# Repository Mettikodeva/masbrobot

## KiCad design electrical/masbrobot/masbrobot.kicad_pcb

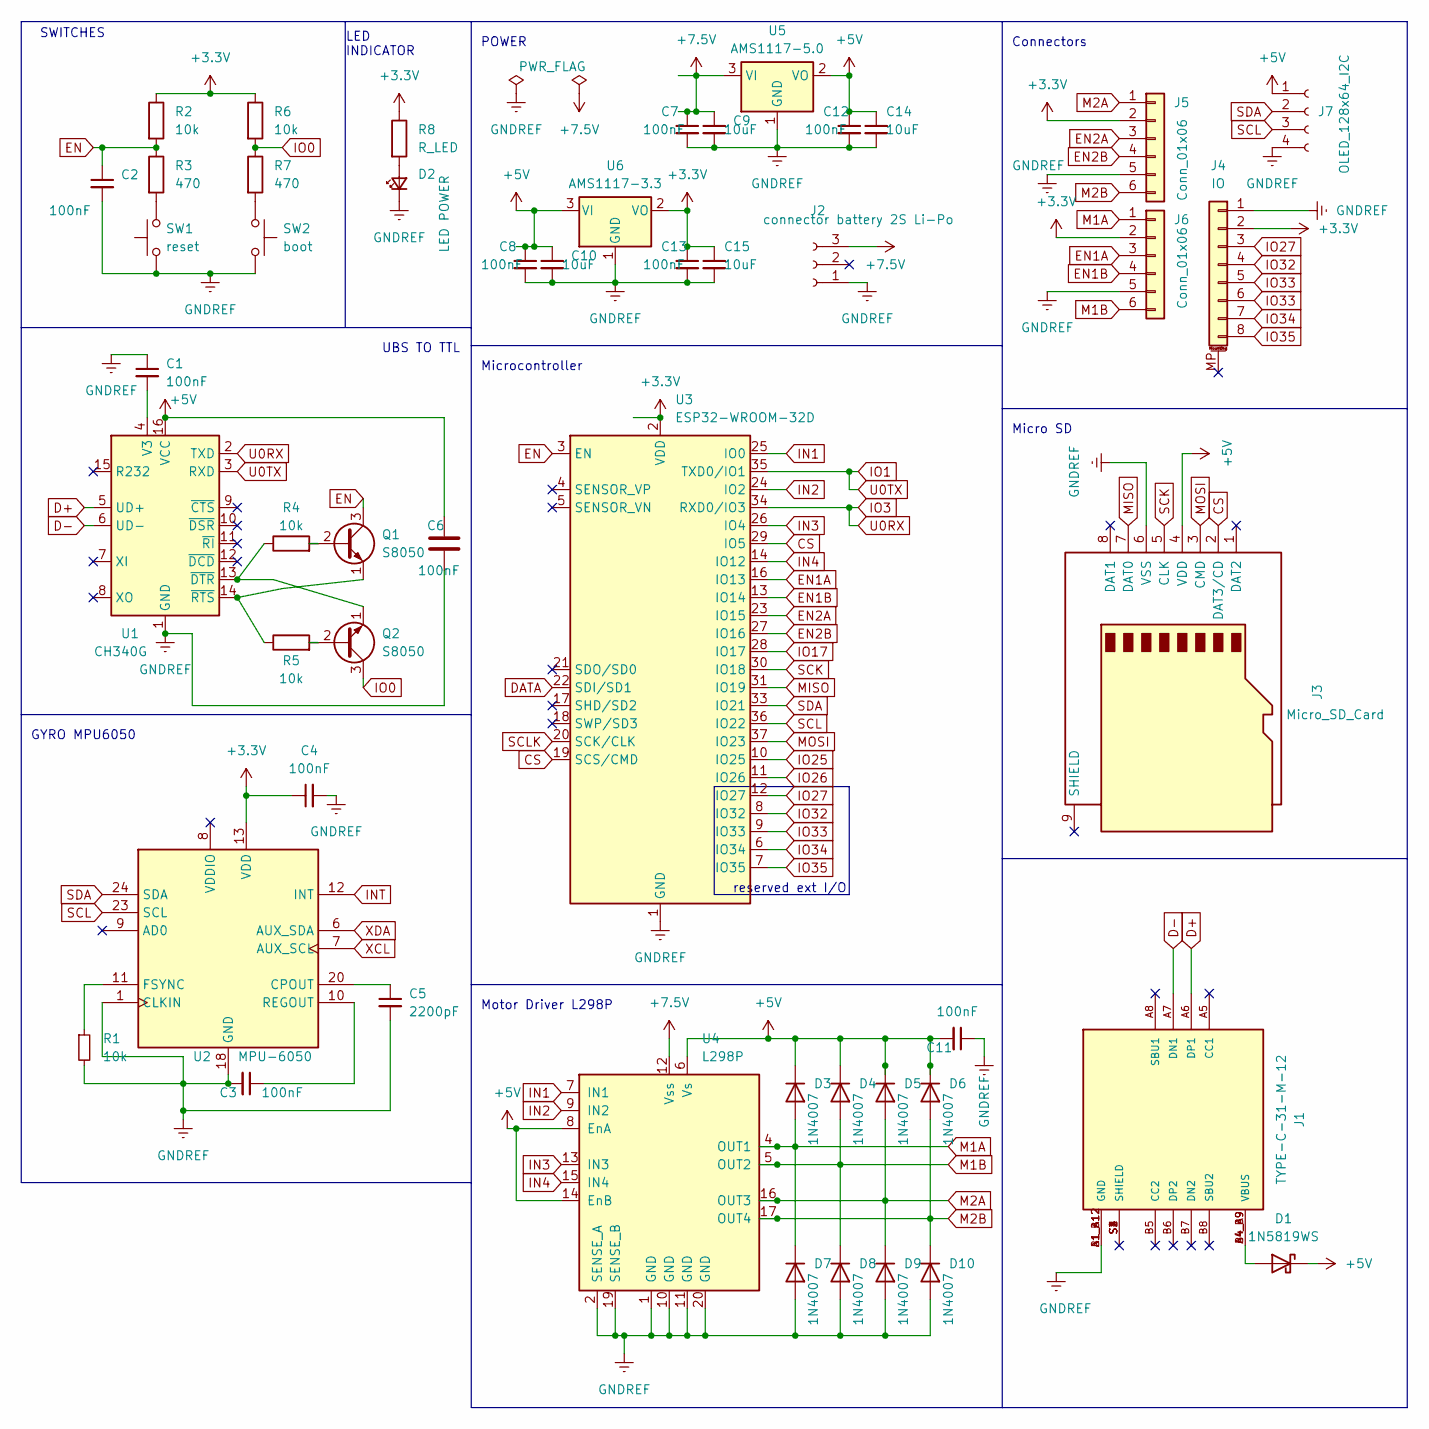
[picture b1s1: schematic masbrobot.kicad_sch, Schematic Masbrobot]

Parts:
C1, C2, C3, C4, C6, C7, C8, C11, C12, C13: 100nF; C_0805_2012Metric
C5: 2200pF; C_0805_2012Metric
C9, C10, C14, C15: 10uF; C_0201_0603Metric
D1: 1N5819WS; D_SOD-323
D2: LED POWER; LED_1206_3216Metric
D3, D4, D5, D6, D7, D8, D9, D10: 1N4007; D_0201_0603Metric
J1: TYPE-C-31-M-12; HRO_TYPE-C-31-M-12; PARTREV 2020.12.08
J2: connector battery 2S Li-Po; JST_XH_B3B-XH-A_1x03_P2.50mm_Vertical
J3: Micro_SD_Card; microSD_HC_Hirose_DM3BT-DSF-PEJS
J4: IO; PinHeader_1x08_P1.27mm_Horizontal
J5, J6: Conn_01x06; JST_GH_BM06B-GHS-TBT_1x06-1MP_P1.25mm_Vertical
J7: OLED_128x64_I2C; JST_GH_BM04B-GHS-TBT_1x04-1MP_P1.25mm_Vertical
Q1, Q2: S8050; TO-92_Inline
R1, R4, R5: 10k; R_0805_2012Metric
R2, R6: 10k; R_1206_3216Metric
R3, R7: 470; R_1206_3216Metric
R8: R_LED; R_0402_1005Metric
SW1: reset; SW_Tactile_SPST_NO_Straight_CK_PTS636Sx25SMTRLFS
SW2: boot; SW_Tactile_SPST_NO_Straight_CK_PTS636Sx25SMTRLFS
U1: CH340G; SOIC-16_3.9x9.9mm_P1.27mm
U2: MPU-6050; InvenSense_QFN-24_4x4mm_P0.5mm
U3: ESP32-WROOM-32D; ESP32-WROOM-32
U4: L298P; SOIC127P1420X360-20N
U5: AMS1117-5.0; SOT-223-3_TabPin2
U6: AMS1117-3.3; SOT-223-3_TabPin2

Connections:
+3.3V: C4.1, C13.1, C15.1, J4.2, J5.2, J6.2, R2.1, R6.1, R8.1, U2.13 (VDD), U3.2 (VDD), U6.2 (VO)
+5V: C6.1, C8.1, C10.1, C11.2, C12.1, C14.1, D1.1 (K), D3.1 (K), D4.1 (K), D5.1 (K), D6.1 (K), J3.4 (VDD), J7.1, U1.16 (VCC), U4.6 (Vs), U4.8 (EnA), U4.14 (EnB), U5.2 (VO), U6.3 (VI)
+7.5V: C7.1, C9.1, J2.3, U4.12 (Vss), U5.3 (VI)
CS: J3.2 (DAT3/CD), U3.19 (SCS/CMD), U3.29 (IO5)
D+: J1.A6 (DP1), U1.5 (UD+)
D-: J1.A7 (DN1), U1.6 (UD-)
DATA: U3.22 (SDI/SD1)
EN: C2.1, Q1.3 (C), R2.2, R3.1, U3.3 (EN)
EN1A: J6.3, U3.16 (IO13)
EN1B: J6.4, U3.13 (IO14)
EN2A: J5.3, U3.23 (IO15)
EN2B: J5.4, U3.27 (IO16)
GNDREF: C1.1, C2.2, C3.2, C4.2, C5.2, C6.2, C7.2, C8.2, C9.2, C10.2, C11.1, C12.2, C13.2, C14.2, C15.2, D2.1 (K), D7.2 (A), D8.2 (A), D9.2 (A), D10.2 (A), J1.A1_B12 (GND), J1.B1_A12 (GND), J2.1, J3.6 (VSS), J4.1, J5.5, J6.5, J7.4, R1.2, SW1.1, SW2.2, U1.1 (GND), U2.1 (CLKIN), U2.18 (GND), U3.1 (GND), U3.15 (GND), U3.38 (GND), U3.39 (GND), U4.1 (GND), U4.2 (SENSE_A), U4.10 (GND), U4.11 (GND), U4.19 (SENSE_B), U4.20 (GND), U5.1 (GND), U6.1 (GND)
IN1: U3.25 (IO0), U4.7 (IN1)
IN2: U3.24 (IO2), U4.9 (IN2)
IN3: U3.26 (IO4), U4.13 (IN3)
IN4: U3.14 (IO12), U4.15 (IN4)
INT: U2.12 (INT)
IO0: Q2.3 (C), R6.2, R7.1
IO1: U1.3 (RXD), U3.35 (TXD0/IO1)
IO3: U1.2 (TXD), U3.34 (RXD0/IO3)
IO17: U3.28 (IO17)
IO25: U3.10 (IO25)
IO26: U3.11 (IO26)
IO27: J4.3, U3.12 (IO27)
IO32: J4.4, U3.8 (IO32)
IO33: J4.5, J4.6, U3.9 (IO33)
IO34: J4.7, U3.6 (IO34)
IO35: J4.8, U3.7 (IO35)
M1A: D3.2 (A), D7.1 (K), J6.1, U4.4 (OUT1)
M1B: D4.2 (A), D8.1 (K), J6.6, U4.5 (OUT2)
M2A: D5.2 (A), D9.1 (K), J5.1, U4.16 (OUT3)
M2B: D6.2 (A), D10.1 (K), J5.6, U4.17 (OUT4)
MISO: J3.7 (DAT0), U3.31 (IO19)
MOSI: J3.3 (CMD), U3.37 (IO23)
unnamed: D1.2 (A), J1.A4_B9 (VBUS), J1.B4_A9 (VBUS)
unnamed: D2.2 (A), R8.2
unnamed: Q1.2 (B), R4.2
unnamed: Q1.1 (E), R5.1, U1.14 (~RTS)
unnamed: Q2.2 (B), R5.2
unnamed: Q2.1 (E), R4.1, U1.13 (~DTR)
unnamed: R3.2, SW1.2
unnamed: R7.2, SW2.1
unnamed: C1.2, U1.4 (V3)
unnamed: C5.1, U2.20 (CPOUT)
unnamed: R1.1, U2.11 (FSYNC)
unnamed: C3.1, U2.10 (REGOUT)
SCK: J3.5 (CLK), U3.30 (IO18)
SCL: J7.3, U2.23 (SCL), U3.36 (IO22)
SCLK: U3.20 (SCK/CLK)
SDA: J7.2, U2.24 (SDA), U3.33 (IO21)
XCL: U2.7 (AUX_SCL)
XDA: U2.6 (AUX_SDA)

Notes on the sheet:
POWER
Connectors
Microcontroller
GYRO MPU6050
LED INDICATOR
reserved ext I/O
Micro SD
Motor Driver L298P
UBS TO TTL
SWITCHES

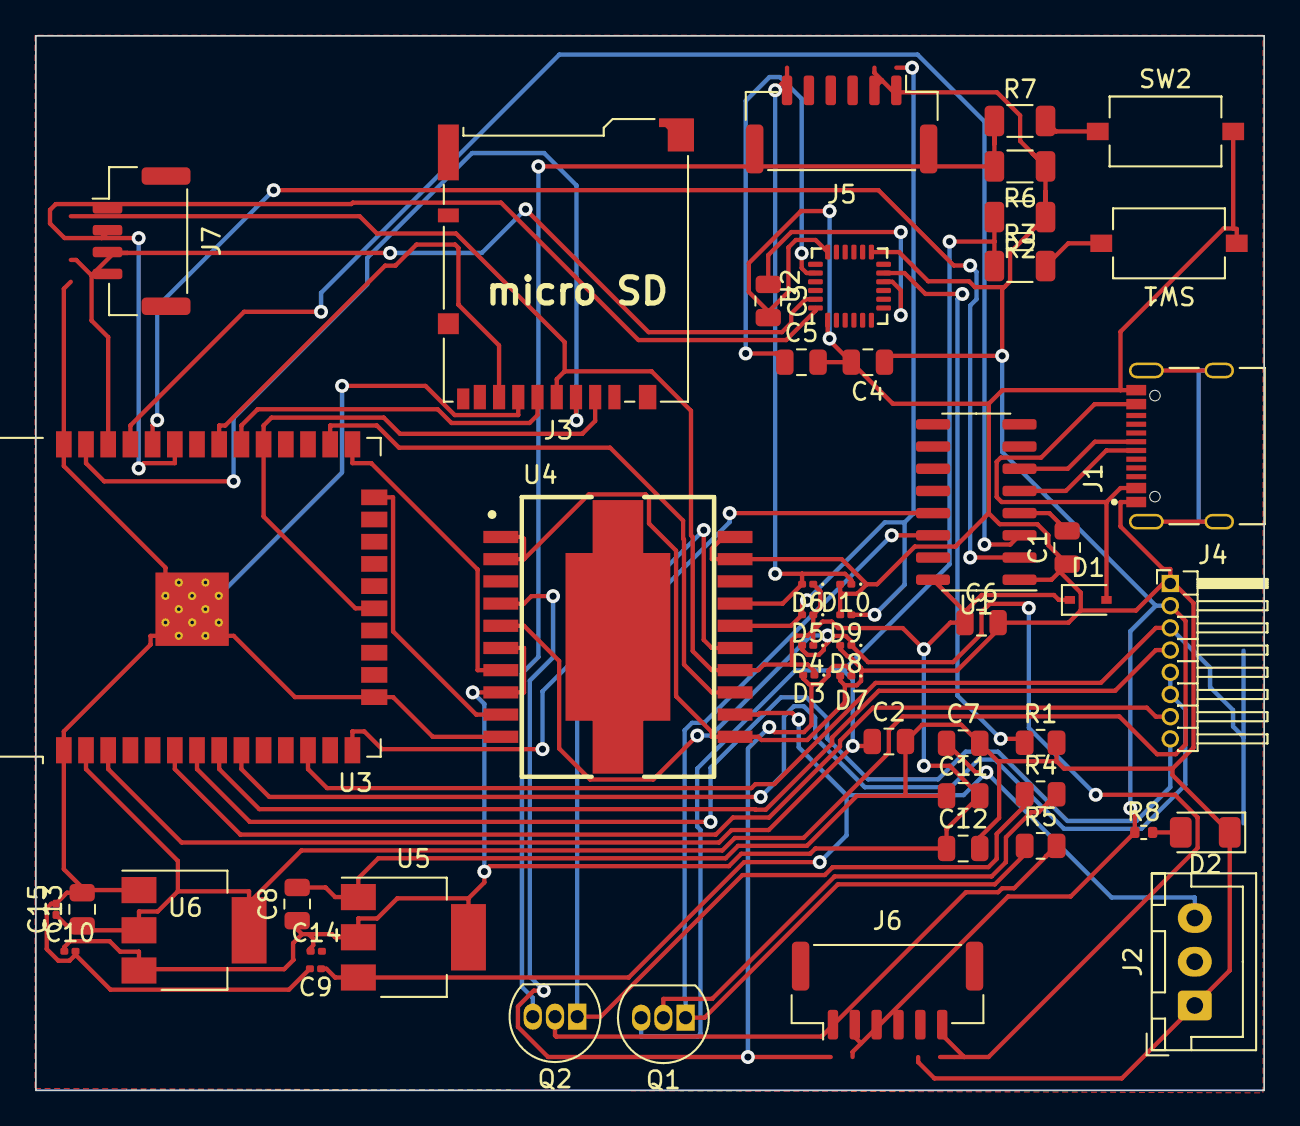
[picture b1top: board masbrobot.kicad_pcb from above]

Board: 2 copper layers, 70.3 x 60.3 mm, 50 parts (0 on the bottom side), 45 nets.

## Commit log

2023-05-16 adding Gyro schematics, some components, product page link, etc
2023-05-16 Update hardware.txt
    Add micro DC motor
2023-05-16 add human-machine diagram
2023-05-29 update schematic and PCB board
2023-05-30 update electrial FIX.
2023-05-30 30% model mechanical
2023-06-04 update smentara
